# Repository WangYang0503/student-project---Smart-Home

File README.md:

# student-project---Smart-Home
Studienprojekt 16/17: Smart Things

Studienprojekt vom Sommersemester 2016 bis zum Wintersemester 2016/2017 an der Abteilung für Software Engineering des Instituts für Softwaretechnologie an der Universität Stuttgart.

Einführung

Dieses Studienprojekt beschäftigt sich mit der Erstellung eines sogenannten Smart Homes, in dem verschiedene "smarte" Alltagsgegenstände miteinander vernetzt sind und über eine gemeinsame Middleware miteinander kommunizieren. Der Fokus des Projekts liegt dabei auf der Anbindung bestehender Geräte an ein Netzwerk, der Entwicklung weiterer solcher Komponenten und der Implementierung diverser "Wenn-Dann"-Regeln, die das Smart Homes auf seine Umgebung reagieren lassen und es damit überhaupt erst lebendig werden lassen. Viele Bestandteile eines "echten" intelligenten Hauses überschreiten jedoch den Umfang eines Studienprojekts in erheblichem Maße, weshalb an dieser Stelle beispielsweise weder eine Lichtsteuerung am 230V-Stromnetz, noch eine realitätsnahe Tür- oder Garagensteuerung realisiert werden kann. Auch die Aufrüstung eines echten Autos zu einem sogenannten "Smart Car", das den Ausgangspunkt vieler Ideen für ein intelligentes Gerätenetzwerk darstellt, sprengt selbstverständlich den Rahmen. Aus diesem Grund beschränkt sich dieses Studienprojekt bei der Entwicklung der verschiedenen Komponente im Allgemeinen auf Miniatur-Modelle und zweckmäßige Nachbauten. Diese genügen trotzdem, um die notwendigen Schnittstellen für die Geräte zu schaffen, eine grundlegende Implementierung zur Umsetzung der "Wenn-Dann"-Regeln vorzunehmen und dem äußeren Betrachter einen Eindruck über die bestehenden Möglichkeiten in dem Smart Home zu verschaffen.

Das Studienprojekt umfasst die folgenden "Smart Things":

Eine Kaffeemaschine
Ein Smart Car
Eine Haus- und eine Garagentür
Die Innen- und Außenbeleuchtung eines Hauses
Einen Rauchmelder

All diese Gegenstände lassen sich zusätzlich über eine Android-App steuern und kontrollieren. Um diese Geräte in Form von "Wenn-Dann"-Regeln auch tatsächlich auch verknüpfen zu können, kommt ein dafür entwickeltes Backend mit Datenbank und leicht zu bedienender Weboberfläche zum Einsatz.

Bei der Kaffeemaschine handelt es sich im Gegensatz zu den anderen Smart Things nicht um ein Modell, sondern um eine richtige Kaffeemaschine in Lebensgröße, die über eine WLAN-Schnittstelle verfügt und somit auch in das Netzwerk eingebunden werden kann. Um die Interaktion der beiden elektronischen Komponenten im Smart Home besser demonstrieren zu können, wurden die Steuerung der Innen- und Außenbeleuchtung und der Haus- und Garagentür  in ein kleines Holzmodell eines Wohnhauses integriert. Bei dem Smart Car handelt es sich um einen Lego Mindstorms-Roboter, der - als Modell eines autonomen, oder zumindest intelligenten Autos - selbstständig fahren und mit anderen Komponenten des Smart Homes kommunizieren kann. Aufgrund der nur aufwändig herzustellenden realen Testbedingungen zur Auslösung des Rauchmelders wird dieser vollständig über eine Android-App auf einem Smartphone simuliert.

Ein weiterer Schwerpunkt dieses Studienprojekts liegt auf der Durchführung von  Aktivitäten des Safety Engineerings, um sicherzustellen, dass bei einer realen Umsetzung des Modells in Lebensgröße so wenig Gefährdungen wie möglich für die Umwelt auftreten. So wurden in den Entwicklungsprozess des Entwickler-Teams verschiedene safety-spezifische Aktivitäten integriert, die die fortwährende Analyse des Gesamtsystems hinsichtlich Safety-Risiken und deren Beseitigung sicherstellen.

Im Folgenden wird ein Überblick über das Projekt gegeben und auf die Hauptverzeichnisse der einzelnen Smart Things verwiesen, in denen sich dann nähere Informationen zum Aufbau, der Installation, zum Betrieb und den implementierten Schnittstellen und Features befinden.

Übersicht der Komponenten

In dem folgenden Schaubild ist der grundlegende Aufbau des durch das Studienprojekt realisierten Smart-Home-Netzwerks dargestellt:

Middleware

Im Zentrum des Netzwerks steht die Middleware. Sie ist grundlegend für das Verwalten der einzelnen Endgeräte, den Smart Things, zuständig. Sie besteht aus einem Server, auf dem die Kaa IoT Development Platform installiert ist und ausgeführt wird. Sie ist in der Lage Software Development Kits (SDKs) in verschiedenen Programmiersprachen zu generieren, darunter auch SDKs für Java, nachdem die entsprechenden Smart-Things auf der dazugehörigen Weboberfläche des Kaa-Servers spezifiziert worden sind. Diese SDKs enthalten die notwendigen Schnitstellen in der jeweiligen Sprache, um dann in der Software der Endgeräte mit der Kaa-Middleware kommunizieren zu können. Die Endgeräte verbinden sich nach dem Start ihrer Software unter Verwendung der zuvor generierten SKDs automatisch mit der Middleware und können bei Bedarf Nachrichten in Form von Events an diese übermitteln. Der Kaa-Server nimmt Nachrichten von den Endgeräten entgegen und verteilt sie an die momentan verfügbaren Endgeräte, die auf Events dieser Art warten (Listener-Prinzip). Diese Art der Kommunikation greift das Backend auf, um an dieser Stelle die Umsetzung der zuvor durch den Anwender festgelegten "Wenn-Dann-Regeln" sicherzustellen.

--> Verzeichnis im Repository

Backend

Um das Smart-Home nun tatsächlich auch “smart” machen zu können, sodass es in bestimmten Situationen von alleine vordefinierte Aktionen auslöst, genügt die direkte Kommunikation der Smart-Things über die Middleware nicht. In diesem Fall müssten Verknüpfungen zur Kommunikation der Smart-Things untereinander umständlich direkt in dem Quellcode der einzelnen Komponenten implementiert werden und wären folglich ohne Neukompilierung des jeweiligen Projekts nicht durch den Endanwender anpassbar. Da dies natürlich eine sehr unkomfortable Art der Konfiguration des Smart Homes darstellt, übernimmt das Backend diese Aufgabe, in welchem der Benutzer über eine Weboberfläche die Regeln, die für sein Smart Home greifen sollen, einstellen und verwalten kann. Bei diesen Regeln handelt es sich dabei um die bereits angesprochenen “Wenn-Dann-Regeln”: Eine Aktion wird vom Smart-Home dann ausgelöst oder ausgeführt, wenn zuvor ein bestimmtes Ereignis oder eine bestimmte Situation aufgetreten ist.

Das Grundgerüst des Backends besteht aus einem Java-Programm, welches selbst auch ein KAA-SDK besitzt und darüber Zugriff auf die Schnittstellen aller Smart-Things erhält. Es ist somit über entsprechende Listener in der Lage, auf die ausgesendeten Events aller Smart-Things zu reagieren und selbst Events an diese Smart-Things auszusenden, die dann dementsprechend Aktionen auslösen können. Ausgehend von dieser Basis besitzt das Backend eine SQLite-Datenbank, in der die Regeln gespeichert werden können. Eine sogenannte “RuleWorker”-Klasse übernimmt auf dem Server die Aufgabe, auf Eingabe eines Eventnamens aus dieser Datenbank alle passenden Regeln herauszusuchen, die diesen Eventnamen als Trigger-Event gespeichert haben, die dazugehörige Aktionsmethode abzufragen auszulösen.

Das Backend besteht weiter aus einer Webserver-Komponente, die sowohl statische Webseiten ausgeben, als auch Ajax-Requests entgegennehmen, verarbeiten und beantworten kann. Für diese Webserver-Komponente gibt es eine Weboberfläche, die die Möglichkeit bietet, über ein Formular neue Regeln anzulegen, diese in einer Tabelle anzuzeigen, zu editieren, zu löschen, zu aktivieren, zu deaktivieren und sie auch direkt über die Weboberfläche auszuführen, ohne dass das zugehörige Triggerevent dafür ausgelöst werden muss. Ferner steht neben einem persistenten Log, das alle Aktionen des Smart-Homes, sowie alle eingehenden und ausgehenden Events und die jeweils ausgelösten Regeln aufzeichnet, auch ein sogenanntes “Live Log” zu Verfügung, das dem Benutzer in Echtzeit auf der Weboberfläche Informationen über die ausgeführten Regeln bietet.

Kurzum bietet das Backend dem Benutzer des Smart Homes über eine Weboberfläche eine sehr komfortable Möglichkeit, “Wenn-Dann-Regeln” für das Smart-Home nach eigenen Wünschen individuell zu verwalten, die die Art und Weise festlegen, auf der die einzelnen innerhalb dieses Projekts entwickelten Smart-Things miteinander interagieren können.

--> Verzeichnis im Repository

Kaffeemaschine

Die Kaffeemaschine, die in diesem Projekt zum Einsatz kommt, ist bereits werksseitig mit einem WLAN-Modul ausgestattet. Damit dieses genutzt werden kann, ist zunächst die Konfiguration der Verbindung mit dem lokalen WiFi-Netzwerk notwendig, welche über die bereits existierende Android-App des Kaffeemaschinenherstellers erfolgen muss. Im Rahmen dieses Projekts wurde die Kommunikation dieser bereits vorhandenen App mit der Kaffeemaschine über das Netzwerk beobachtet und analysiert, sodass es gelungen ist, die Kommunikation zu großen Teilen zu entschlüsseln und die Hersteller-App damit durch eine eigens entwickelte Software zu ersetzen. Da die Kaffeemaschine aufgrund fehlender Möglichkeiten, diese zu programmieren oder weiter zu konfigureren nicht in der Lage ist, selbstständig mit der Middleware zu kommunizieren, wurde als Teil des Studienprojekts ein Java-Programm, der sogenannte "CoffeeServer", entwickelt, das zum einen die Kommunikation mit der Middleware übernimmt und zum anderen Befehle an die Kaffeemaschine schickt und Statusmeldungen von ihr empfängt, um sie mit dem Smart Home verknüpfen zu können. Dabei wurden sämtliche zuvor entschlüsselte Kommunikationsvorschriften für die Kaffeemaschine in eine Java-Bibliothek ausgelagert ("SmartCoffeeAPI"), die vom CoffeeServer verwendet wird und es erlaubt, über WiFi die Verbindung mit dem WLAN-Modul der Kaffeemaschine aufzubauen, die Maschine anzusteuern und Statusmeldungen von ihr zu empfangen.

Die Kaffeemaschine ist so in der Lage, Statusmeldungen über den aktuellen Zustand (beispielsweise Bereit, Kochend, Mahlend) an die Middleware und damit an andere Smart Things zu senden und gleichtig von diesen Befehle zu empfangen, beispielsweise Kaffee kochen, Brühstärke ändern und Tassenzahl ändern.

--> Verzeichnis im Repository

Smart Car

Das sogenannte "Smart Car" wird in diesem Studienprojekt modellhaft über einen Lego-Mindstorm (EV3) realisiert, der ganz grob die ungefähre Bauform eines Fahrzeugs aufweist. Auf dem "programmieren intelligenten Stein" (Mindstorm-Brick) des Mindstorms, der das logische Herz des Lego-Roboters darstellt, ist das javafähige Betriebssystem Lejos installiert. Damit ist es möglich, Java-Programme auf dem Mindstorm auszuführen. Die EV3-Serie erlaubt zudem den Anschluss eines wifi-fähigen USB-Sticks, über den zusammen mit der entsprechenden Implementierung dann die Kommunikation mit dem Kaa-Server erfolgen kann. Wie bei den meisten anderen der zu dem Studienprojekt gehörenden Smart-Things kann somit das vom Kaa-Server für den Mindstorm generierte SDK in ein Java-Programm eingebettet werden und über das Netzwerk mit der Middleware kommunizieren.

Das Smart Car ist beispielsweise in der Lage selbstständig über Lichtsensorik einer farbigen Linie zu folgen, wenn dies beispielsweise von der App veranlasst wird, auf Befehl anzuhalten, anhand der Linienfarbe zu erkennen, wo sich das Auto gerade aufhält (zum Beispiel, dass es sich in der Nähe der Garage befindet), unter Verwendung  eines drehbaren Ultraschallsensors Hindernissen auszuweichen, aktuelle Statussignale an die Middleware zurückzumelden und unter Verwendung von Bodenmarkierungen in die Garage einzuparken.

--> Verzeichnis im Repository

Haus- und Garagentüren

Die hier zum Einsatz kommenden Türen - jeweils eine Haustüre und eine Garagentüre - sind Teil des Holzmodells eines Hauses, das zur Veranschaulichung dieser Komponente und der Lichtsteuerung angefertigt wurde. Ähnlich wie bei dem Smart Car wird auch hier die Steuerung der beiden Türen über einen Lego-Roboter (EV3) realisiert, dessen Mindstorm-Brick mit einem WiFi-USB-Stick ausgestattet ist und das javafähige Betriebssystem Lejos installiert hat. Die Türen werden über Lego-Motren, die zu diesem Roboter gehören, angesteuert: Eine Konstruktion aus einem Getriebe mit mehreren Zahnrädern erlaubt es dem Motor, die Haustür vorsichtig zu öffnen und wieder zu schließen. Eine Art Flaschenzug mit einer Seilwinde, die an einem Motor auf dem Dach der Garage befestigt ist, erlaubt es einem anderen Motor, der mit demselben Mindstorm verknüpft ist, das Garagentor zu öffnen und zu schließen. Zusätzlich wird der Status des Garagentors (Offen oder Geschlossen) durch einen Ultraschallsensor erfasst.

Die Haus- und Türsteuerung kann so den aktuellen Status der Türen an die Middleware melden und gleichzeitig von anderen Smart Things Befehle empfangen und ausführen, wie das Öffnen und Schließen der Türen.

--> Verzeichnis im Repository

Innen- und Außenbeleuchtung

Neben der Türsteuerung wird das Hausmodell auch mit verschiedenen Lichtern versorgt, die sowohl außen vom Haus, als auch innen in Form von RGB-LEDs angebracht sind. Diese werden über eine Verstärkerplatine, auf der Transistorschaltungen realisiert sind, um die LEDs mit ausreichend Strom zu versorgen, geschaltet. Diese Platine ist wiederum mit einem Raspberry Pi 3 verknüpft, das Raspbian als Betriebssystem verwendet und somit in der Lage ist, über ein darauf ausgeführtes Java-Programm die LEDs über die Verstärkerplatine durch das Ansteuerun der GPIO-Ports an- und auszuschalten. Das Raspberry Pi besitzt bereits werkseitig ein integriertes WLAN-Modul und kann somit direkt mit dem Smart-Home-Netzwerk verknüpft werden und ebenso ein Kaa-SDK verwenden. Die im Rahmen des Studienprojekts erstellte Software auf dem Raspberry Pi unterstützt die Zuordnung der LEDs zu Räumen, sodass verschiedene LED-Gruppen in einem Raum zusammengefasst und dann von anderen Smart Things gemeinsam als Gruppe angesteuert werden können. Die Konfiguration und Aufteilung der LEDs an den verschiedenen Pins in Räume erfolgt dabei über eine XML-Datei, die von der Software auf dem Raspberry zu Beginn eingelesen wird. Da es sich bei den LEDs um RGB-Leds handelt, kann auch die Farbe der Beleuchtung durch die softwareseitige Ansteuerung verändert werden.

Die Lichtsteuerung auf dem Raspberry kann so den aktuellen Status der Beleuchtung (zum Beispiel An, Aus, Farbe, Helligkeit) an die Middleware senden und im Gegenzug Befehle anderer Smart Things entgegennehmen, wie das Dimmen der LED-Helligkeit, das Verändern der Farben und das Ein- und Ausschalten einzelner LEDs oder ganzer zu Räumen zusammengefasster LED-Gruppen.

--> Verzeichnis im Repository

Rauchmelder

Auch ein Rauchmelder soll als Smart Thing in das Smart-Home-Netzwerk integriert werden. Allerdings wurde aus Gründen des Aufwands und der nur schwer herzustellenden notwendigen Testbedingungen darauf verzichtet, einen echten Rauchmelder, wie man ihn aus den Baumärkten kennt, umzurüsten. Stattdessen wird der Rauchmelder über eine Android-App simuliert, die auf einem Smartphone oder Tablet ausgeführt wird. Innerhalb dieser App kann so mit einem Knopfdruck ein Feueralarm ausgelöst werden, dere von einem schrillen Ton begeleitet wird. Der Alarm hält so lange an, bis er durch einen erneuten Knopfdruck in der App deaktiviert wird. Diese App integriert ebenfalls ein Kaa-SDK, das jedoch im Gegensatz zu den bisher verwendeten Java-SDKs speziell auf Android-Geräte ausgerichtet ist. Damit ist auch hier eine direkte Kommunikation über die Middleware zu anderen Smart Things möglich.

Wird bei der Rauchmeldersimulation der Feueralarm ausgelöst, sendet die App ein entsprechendes Event an die Middleware, welches diese wiederum an andere Geräte verteilt, die dann entsprechend auf den Alarm reagieren können, beispielsweise durch Aktivierung einer Notbeleuchtung. Endet der Alarm, wird erneut die Middleware verständigt, um etwaige ergriffene Maßnahmen anderer Smart Things wieder abzubrechen, sofern nötig.

--> Verzeichnis im Repository

Android-App

Als zentrale Benutzerschnittstelle des Smart-Home-Netzwerks wird im Rahmen des Studienprojekts eine Android-App entwickelt, über die alle Smart-Things eingesehen, abgefragt und kontrolliert werden können sollen. Ähnlich wie der Rauchmelder implementiert auch die App ein speziell auf Android ausgelegtes Kaa-SDK, dass es dem Nutzer ermöglicht, über das Netzwerk mit der Middleware zu kommunizieren.

Die App empfängt nahezu alle Kaa-Events der mit dem Netzwerk verknüpften Smart-Things und kann so zu jeder Komponente Statusmeldungen einsehen und Benachrichtigungen dieser reagieren, beispielsweise wenn das Kochen des Kaffees abgeschlossen ist. Darüberhinaus kann über die App auch manuell auf die Smart Things Einfuss genommen werden, um beispielsweise des Starten oder Stoppen des Smart Cars zu veranlassen, Kaffeeeinstellungen zu konfigurieren, Lichter ein-, aus- und umzuschalten oder die Türen zu öffnen oder zu schließen. Darüberhinaus erlaubt es die App, auch Timer für das Kaffeekochen festzulegen, sodass der Benutzer bereits im Voraus konfigurieren kann, zu welcher Uhr- oder Tageszeit automatisch Kaffee gekocht werden soll, sofern natürlich ausreichend Ressourcen wie Kaffee und Wasser vorhanden sind.

--> Verzeichnis im Repository

Integrierte Regeln

Neben der Steuerung der Smart Things über die Android-App ist es eines der Hauptziele dieses Studienprojekts, die Interaktion der intelligenten Geräte untereinander über die Middleware zu realisieren. So sollen nach dem Prinzip der "Wenn-Dann-Regeln" zuvor definierte Aktionen ausgelöst werden, wenn das Smart Home eine bestimmte Situation registriert. Diese Art der Regeldefinition erfolgt von Seiten des Benutzers auf der Weboberfläche des Backends, welches im Anschluss dann in der Lage ist, auch diese Regeln anzuwenden. "Wenn das Smart Car am Smart Home ankommt, soll die Kaffeemaschine Kaffee kochen, damit der Besitzer diesen trinken kann, wenn er das Haus betritt." ist ein typisches Beispiel für eine solche Regel.

Unabhängig von der Android-App wurden die folgenden Interaktionen ihm Rahmen dieses Projekts implementiert:

Wenn-Dann-Regel
Auslösende Komponente
Reagierende Komponente
Anmerkungen

Wenn das Auto am Smart Home ankommt, soll Kaffee gekocht werden.
Smart Car
Kaffeemaschine
Der Grundgedanke bei dieser Regel ist, dass sich der Besitzer des Smart Homes nach einem anstrengenden Arbeitstag bei einer Tasse frischem Kaffee entspannen möchte, sobald er zu Hause angekommen ist.

Wenn das Auto an der Garage ankommt, soll sich das Garagentor öffnen.
Smart Car
Türsteuerung
Wenn das Auto die Garage erreicht, ist davon auszugehen, dass es auch in die Garage eingeparkt werden soll. Deshalb öffnet sich das Tor automatisch, um dem Besitzer lästiges manuelles Öffnen zu ersparen.

Wenn ein Feueralarm ausgelöst wird, soll die Hausbeleuchtung eingeschaltet werden und rot leuchten.
Rauchmelder
Lichtsteuerung
Durch das Einschalten der Beleuchtung soll dem Besitzer des Smart Homes zum einen das Haus ausgeleuchtet werden, damit er sich auch nachts sofort in der Notsituation zurecht finden kann und nicht erst den Lichtschalter suchen muss; zum anderen soll ihm mit dem roten Leuchten, wie man es auch aus Science-Fiction-Filmen kennt, zusätzlich der Ernst der Lage deutlichgemacht werden.

Wenn ein Feueralarm ausgelöst wird, sollen die Haus- und Garagentüre geöffnet werden.
Rauchmelder
Türsteuerung
Um dem Besitzer des Smart Homes im Falle eines Feueralarms frühzeitig mögliche Fluchthindernisse aus dem Weg zu räumen, sollen die Haus- und die Garagentüre automatisch geöffnet werden.

Die "Auslösende Komponente" bezeichnet das Smart Thing, das die "Wenn"-Aufgabe der Regel übernimmt und die Situation erkennt, auf die reagiert werden soll. Die "Reagierende Komponente" bezeichnet dagegen das Smart Thing, das den "Dann"-Teil der Regel übernimmt und auf die eingetretene Situation mit einer zuvor definierten Aktion reagiert.

Technische Übersicht

In Laufe des Projekts wurden einige verschiedene Techniken und Entwicklungswerkzeuge eingesetzt. An dieser Stelle soll darüber eine Übersicht gewährt werden.

Java

Der allergrößte Teil der Software dieses Projekts ist in Java 8 geschrieben. Dies betrifft vor allem die Software der Kaffeemaschine, bestehend aus dem CoffeeServer und der SmartCoffeeAPI, und die Lichtsteuerung, welche in "reinem" Java, also ohne weitere plattformabhängige Bibliotheken und Erweiterungen, verfasst sind. Die Software der Kaffeemaschine kann damit als ausführbare JAR-Datei auf einem nahezu beliebigen Rechner ausgeführt werden. Im Rahmen des Studienprojekts wurde speziell ein Raspberry PI 3 (Model B) mit installierter JRE als Zielplattform für den CoffeeServer vorgesehen, auf dem dann auch die Lichtsteuerung ausgeführt werden soll, die die GPIO-Pins des Raspberrys verwendet, um die LEDs, die die Beleuchtung des Smart Homes repräsentieren, über eine Verstärkerplatine anzusteuern. Als Entwicklungsumgebungen wurden hierfür IntelliJ IDEA von JetBrains und Eclipse eingesetzt.

Android

Die App zur Gesamtsteuerung und der Rauchmelder-Simulator sind Android-Apps, die in Java 8 geschrieben worden sind. Zur Ausführung auf Android-Geräten setzen diese ein Minimum-Android-SDK-Level von 16 ("Jelly Bean") voraus, Ziel-SDK-Level ist 24 ("Nougat"). Zur Entwicklung wurde ausschließlich Android Studio von JetBrains eingesetzt, die Apps werden in diesem mit Gradle gebuildet.

LeJOS

Das Smart Car und die Türsteuerung für die Haus- und Garagentüre sind jeweils über einen Lego-Mindstorm EV3 realisiert, über deren "intelligenten Stein" die Kommunikation mit der Middleware umgesetzt wird und die die dazugehörenden Lego-Sensoren und Lego-Motoren einsetzen, um die Umgebung zu erfassen und zu beeinflussen. Da der Kaa-Server auf der Middleware nur für bestimmte Programmiersprachen SDKs generieren kann, die für die Software der Smart Things zwingend notwendig sind, um mit der Middleware interagieren zu können, war es erforderlich, das Standardbetriebssystem der Mindstorms, das nur C-ähnliche Programme ausführen kann, zu entfernen und stattdessen das Betriebssystem LeJOS (LeJOS EV3 0.9.1-beta) über eine SD-Karte aufzuspielen, das die Ausführung von Java-Programmen als ausführbare JAR-Dateien ermöglicht, die mit einer entsprechenden API für EV3-Mindstorms ausgestattet worden sind. Als Entwicklungsumgebungen wurden hierfür IntelliJ IDEA von JetBrains und Eclipse eingesetzt.

Maven

Als Build-Management-Tool wird in diesem Studienprojekt Apache Maven eingesetzt, das zahlreiche zentrale Aufgaben übernimmt und dessen Zyklus jeweils für jedes Smart Thing in ein eigenes Submodul aufgeteilt ist. Sämtliche Kaa-SDKs werden bei einem Aufruf von Mavens Goal "clean install" zunächst aus dem Sammelordner für die SKDs in das lokale Maven-Repository installiert und stehen dann den anderen Komponenten, die die entsprechenden SDKs als Abhängigkeit eingetragen haben, zum Kompilieren zur Verfügung. Nach der Installation dieser SDKs buildet der Maven-Prozess die Software und erstellt aus dem CoffeeServer, welcher abhängig von der SmartCoffeeAPI ist, der Lichtsteuerung, der Software für das SmartCar und der Software für die Türsteuerung jeweils ausführbare JAR-Dateien, welche in einen build-Ordner im Hauptverzeichnis kopiert werden. Dabei werden bestehende softwaretechnische Abhängigkeiten und zusätzlich benötigte APIs, wie beispielsweise LeJOS "ev3classes" für die Programmierung der EV3-Mindstorms in Java und die zahlreichen Kaa-SDKs, berücksichtigt und mit in die JAR-Dateien gepackt ("jar with dependencies"). Auch die beiden Android-Apps (App zur Hauptsteuerung und Rauchmelder) werden zu APK-Dateien gebuildet; das geschieht allerdings über das in Android-Studio eingebettete Gradle, dessen Build-Prozess jeweils von Maven mitgestartet wird. Abhängigkeiten der Android-Apps sind daher nicht in Maven direkt integriert, sondern in den dazugehörigen Gradle-Build-Dateien in Android Studio. Die generierten APK-Dateien werden nach Abschluss der Kompilierung ebenfalls in den zentralen Build-Ordner im Hauptverzeichnis kopiert.

Bevor die einzelnen Software-Komponenten gebuildet werden, führt Maven jeweils etwaige angelegte Unit-Tests und statische Codeanalysen mittels Checkstyle und FindBugs durch und reklamiert etwaige Testfehlverschläge, Verstöße gegen den als Checkstyle-XML-Datei definierten Styleguide oder gefundene Bug-Muster.

Bei den Smart Things, die auf einem Lego Mindstorms ausgeführt werden - also dem Smart Car und der Türsteuerung - ist es notwendig, die generierten ausführbaren JAR-Dateien auf den im selben Netzwerk befindlichen Lego-Mindstorm mittels SCP zu kopieren. Auch dies kann Maven auf Wunsch übernehmen: Durch einen Aufruf des Goals "clean intall antrun:run" im Unterverzeichnis des jeweiligen SmartThings wird die JAR-Datei generiert und automatisch auf den "intelligenten Stein" kopiert, wo sie dann manuell über den LeJOS-Explorer auf dem Mindstorm ausgeführt werden kann.

Weitere Infos zu Maven und dem Build-Management befinden sich im Dokumentationsordner über das Build-Management im Repository in Form einer Präsentation.

Git

Git ist die Software zu Versionsverwaltung, die in dem Studienprojekt zum Einsatz kommt. Als Webanwendung für das zentrale Git-Repository auf dem Uniserver kommt GitLab zum Einsatz, welches mit JIRA von Atlassian, der von den Projektteilnehmern verwendeten Webanwendung zum Bugtracking und Projektmanagement, direkt verschaltet ist. Auf diese Weise kann des Bugtracking und Umsetzen von User Stories und Tasks anhand der Commit-Messages analog zu den Commits im zentralen Git-Repository vorgenommen werden.

Die zentrale ".gitignore"-Datei befindet sich im Hauptverzeichnis des Repositories.

Jenkins

Um das gesamte Projekt fortlaufend nach jedem Commit anhand des Maven-Zyklusses automatisiert bauen und so frühzeitig Inkompatiblitäten und Softwarefehler erkennen zu können, kommt bei diesem Studienprojekt Jenkins als Continuous-Integration-Server zum Einsatz. Dieser Uni-Server hat direkten Zugriff auf das zentrale Git-Repository und kann so den Build-Prozess direkt nach jedem Commit anhand der vom Repository bezogenen Dateien ausführen.

Im Falle eines Build-Fehlschlags aufgrund von im Maven-Zyklus aufgetretenen Fehlern werden die Teilnehmer des Studienprojekts umgehend per E-Mail über die bestehenden Proleme unterrichtet, damit diese möglichst zeitnah behoben werden können.

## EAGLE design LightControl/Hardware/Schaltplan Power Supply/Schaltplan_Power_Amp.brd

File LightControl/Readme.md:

# LightControl
## Beschreibung
Bei diesem Smart Thing handelt es sich um eine von uns in verminderter Größe hergestellten Simulation der Beleuchtung in einem SmartHome. Durch diese Simulation können wir Lichter im Haus ansteuern und leuchten lassen. Die Farbe der LEDs lässt sich über die App einstellen. Auch durch den SmokeDeviceAlarm können die LEDs zum Leuchten gebracht werden. Innerhalb dieses Projekts war es das Ziel, die Beleuchtung zu planen, zu erstellen und dann die Steuerung zu programmieren. Auch war die Kommunikation der Steuerungmit der App und dem Netzwerk wichtig. 

## Funktionen
Die LightControl besitzt folgende Funktionen:
### Befehle an die LightControll
Die LightControl wartet fortlaufend auf Befehle, die über die Middleware bei ihr eintreffen und reagiert anschließend auf diese. Folge Befehle können an die Garage gesendet werden:
- Lights on: Lichter gehen an.
- Lights off: Lichter gehen aus.
- Lights alarm: Lichter gehen an, da der Rauchmelder Alarm geschlagen hat.

### Informationen von der LightControl
Die LightControl besitzt verschiedene Zustände, die abgefragt werden können:
- LEDInfoRequest
- LEDInfObject(*ID,isRGB,red,green,blue,brightness*)
- LEDInfoResponse(*LEDInfoList*)
- RoomInfoRequest
- RoomInfoReponse(*RoomInfoList*)
- addRoom(*roomID*)
- removeRoom(*roomID*)
- addLight(*lightID,roomID,slot*)
- addRGBLight(*lightID,roomID,slotRed,slotGreen,slotBlue*)
- removeLight(*lightID*)
- setBrightness(*lightID,brightness*)
- setcolor(*lightID,red,green,blue*)
- setRoomBrightness(*roomID,brightness*)
- setRoomColor(*roomID,red,green,blue*)

## Installation und Betrieb
Um die Lichtersteuerung zu benutzen, muss sie am Strom angeschlossen sein. Zudem muss der [Raspberry Pi](https://www.raspberrypi.org/) angeschlossen sein. Nun kann man die Lichter über die App steuern. [Anleitung](https://gilbert.informatik.uni-stuttgart.de/StuPro2016/SmartHomeMain/blob/dev/LightControl/readme.txt)

## Aufbau
Die LightControl besteht aus einem Raspberry Pi, LEDs und einer Verstärkerplatine.

### Hardware
Bei der in diesem Projekt verwendeten Raspberry Pi handelt es sich um einen [Raspberry Pi 3](https://www.raspberrypi.org/products/raspberry-pi-3-model-b/ "Website über den Raspberry Pi 3") EV3 des Herstellers [Raspberry](https://www.raspberrypi.org/ "Webseite des Raspberry"). 

### Kaa-Schnittstelle

#### Ausgehend

| Event | Syntax | Parameter | Beschreibung |
|-------|--------|-----------|--------------|
| LEDinfoResponse | InfoResponseEvent(LEDInfoList) | LEDInfoList(smart_things.light.schema.LEDInfoObjekt) |Dieses Event wird gesendet sobald die Middleware Kaa ein InfoRequesrEvent sendet. |
| RoomInfoResponseEvent |  RoomInfoResponseEvent(RoomInfoList) | RoomInfoList(array,items string) |Dieses Event wird gesendet sobald die Middleware Kaa ein RoomInfoRequestEvent sendet. |

#### Eingehend

| Event | Syntax | Parameter | Beschreibung |
|-------|--------|-----------|--------------|
| LEDInfoObjekt | LEDInfoObjekt(ID,isRGB,red,green,blue,brightness) | ID(string),isRGB(boolean),red(int),green(int),Blue(int),brightness(int) |Dieses Event wird empfangen sobald die Middleware Kaa die Lichter ansteuert. |
| RoomInfoRequest | -- | -- |Dieses Event wird empfangen sobald die Middleware Kaa Informationen über die Räume verlangt. |
| addRoom | addRoom(roomID)  | roomID(int)  |Dieses Event wird empfangen sobald über die App ein neuer Raum erstellt wird. |
| removeRoom | removeRoom(roomID)  | roomID(int) |Dieses Event wird empfangen sobald über die App ein Raum gelöscht wird. |
| addLight | addLight(lightID) | lightID(int),roomID(int),slot(int) | Dieses Event wird empfangen sobald über die App ein neues Licht eingerichtet wird. |
| addRGBLight | addRGBLight(lightID,roomID,slotRed,slotGreen,slotBlue) | lightID(int),roomID(int),slotRed(int),slotGreen(int),slotBlue(int) |Dieses Event wird empfangen sobald über die App ein neues farbiges LED eingerichtet wird. |
| removeLight | removeLight(lightID) | lightID(int) | Dieses Event wird empfangen sobald über die App ein bestimmtes Licht entfernt wird. |
| setBrightness | setBrightness(lightID,brightness) | lightID(int),brightness(int) |Dieses Event wird empfangen wenn über die App die Helligkeit der LEDs geändert wird. |
| setColor | setColor(lightID,red,green,blue) | lightID(int),red(int),blue(int) |Dieses Event wird empfangen wenn der Benutzer über die App die Farbe eines bestimmten Lichtes ändert. |
| setRoomBrightness | setRoomBrightness(roomID,brightness) | roomID(int),brightness(int) |Dieses Event wird empfangen wenn der Benutzer über die App die Helligkeit in einem ganzen Raum ändert. |
| setRoomColor | setRoomColor(roomID,red,green,blue) | roomID(int),red(int),green(int),blue(int) |Dieses Event wird empfangen sobald der Benutzer der App die Farbe der LEDs in einem kompletten Raum ändert. |

## Anmerkungen
Netzteil ist intern von einem Teammitglied und sollte durch eines der Universität ersetzt werden.

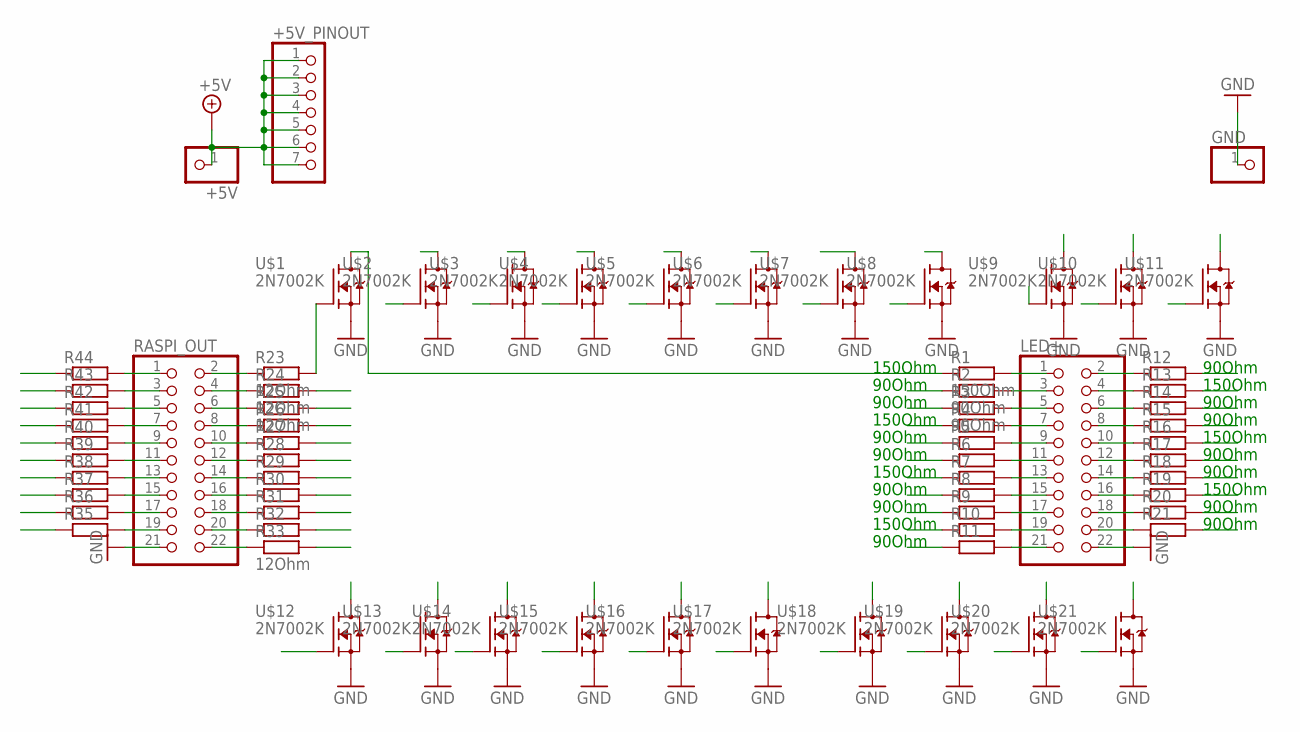
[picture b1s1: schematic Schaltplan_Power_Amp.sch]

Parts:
+5V: PINHD-1X1; 1X01
+5V_PINOUT: PINHD-1X7; 1X07
GND: PINHD-1X1; 1X01
LED+: PINHD-2X11; 2X11
R1: 150Ohm; M1206
R2, R3: 90Ohm; M1206
R4, R5, R6, R7, R8, R9, R10, R11, R12, R13, R14, R15, R16, R17, R18, R19, R20, R21, R26, R27, R28, R29, R30, R31, R32, R35, R36, R37, R38, R39, R40, R41, R42, R43, R44: R-EU_M1206; M1206
R23, R24, R25, R33: 12Ohm; M1206
RASPI_OUT: PINHD-2X11; 2X11
U$1, U$2, U$3, U$4, U$5, U$6, U$7, U$8, U$9, U$10, U$11, U$12, U$13, U$14, U$15, U$16, U$17, U$18, U$19, U$20, U$21: 2N7002K; SOT23

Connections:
+5V: +5V.1, +5V_PINOUT.1, +5V_PINOUT.2, +5V_PINOUT.3, +5V_PINOUT.4, +5V_PINOUT.5, +5V_PINOUT.6, +5V_PINOUT.7
DRAIN2: R2.1, U$2.3 (D)
DRAIN3: R3.1, U$3.3 (D)
DRAIN4: R4.1, U$4.3 (D)
DRAIN5: R5.1, U$5.3 (D)
DRAIN6: R6.1, U$6.3 (D)
DRAIN7: R7.1, U$7.3 (D)
DRAIN8: R8.1, U$8.3 (D)
DRAIN9: R9.1, U$9.3 (D)
DRAIN10: R10.1, U$10.3 (D)
DRAIN11: R11.1, U$11.3 (D)
DRAIN12: R12.2, U$12.3 (D)
DRAIN13: R13.2, U$13.3 (D)
DRAIN14: R14.2, U$14.3 (D)
DRAIN15: R15.2, U$15.3 (D)
DRAIN16: R16.2, U$16.3 (D)
DRAIN17: R17.2, U$17.3 (D)
DRAIN18: R18.2, U$18.3 (D)
DRAIN19: R19.2, U$19.3 (D)
DRAIN20: R20.2, U$20.3 (D)
DRAIN21: R21.2, U$21.3 (D)
GATE2: R24.2, U$2.1 (G)
GATE3: R25.2, U$3.1 (G)
GATE4: R26.2, U$4.1 (G)
GATE5: R27.2, U$5.1 (G)
GATE6: R28.2, U$6.1 (G)
GATE7: R29.2, U$7.1 (G)
GATE8: R30.2, U$8.1 (G)
GATE9: R31.2, U$9.1 (G)
GATE10: R32.2, U$10.1 (G)
GATE11: R33.2, U$11.1 (G)
GATE12: R44.1, U$12.1 (G)
GATE13: R43.1, U$13.1 (G)
GATE14: R42.1, U$14.1 (G)
GATE15: R41.1, U$15.1 (G)
GATE16: R40.1, U$16.1 (G)
GATE17: R39.1, U$17.1 (G)
GATE18: R38.1, U$18.1 (G)
GATE19: R37.1, U$19.1 (G)
GATE20: R36.1, U$20.1 (G)
GATE21: R35.1, U$21.1 (G)
GND: GND.1, LED+.22, RASPI_OUT.21, U$1.2 (S), U$2.2 (S), U$3.2 (S), U$4.2 (S), U$5.2 (S), U$6.2 (S), U$7.2 (S), U$8.2 (S), U$9.2 (S), U$10.2 (S), U$11.2 (S), U$12.2 (S), U$13.2 (S), U$14.2 (S), U$15.2 (S), U$16.2 (S), U$17.2 (S), U$18.2 (S), U$19.2 (S), U$20.2 (S), U$21.2 (S)
unnamed: R44.2, RASPI_OUT.1
unnamed: R43.2, RASPI_OUT.3
unnamed: R42.2, RASPI_OUT.5
unnamed: R41.2, RASPI_OUT.7
unnamed: R40.2, RASPI_OUT.9
unnamed: R39.2, RASPI_OUT.11
unnamed: R38.2, RASPI_OUT.13
unnamed: R37.2, RASPI_OUT.15
unnamed: R36.2, RASPI_OUT.17
unnamed: R35.2, RASPI_OUT.19
unnamed: R23.1, RASPI_OUT.2
unnamed: R24.1, RASPI_OUT.4
unnamed: R25.1, RASPI_OUT.6
unnamed: R26.1, RASPI_OUT.8
unnamed: R27.1, RASPI_OUT.10
unnamed: R28.1, RASPI_OUT.12
unnamed: R29.1, RASPI_OUT.14
unnamed: R30.1, RASPI_OUT.16
unnamed: R31.1, RASPI_OUT.18
unnamed: R32.1, RASPI_OUT.20
unnamed: R33.1, RASPI_OUT.22
unnamed: LED+.1, R1.2
unnamed: LED+.3, R2.2
unnamed: LED+.5, R3.2
unnamed: LED+.7, R4.2
unnamed: LED+.9, R5.2
unnamed: LED+.11, R6.2
unnamed: LED+.13, R7.2
unnamed: LED+.15, R8.2
unnamed: LED+.17, R9.2
unnamed: LED+.19, R10.2
unnamed: LED+.21, R11.2
unnamed: LED+.2, R12.1
unnamed: LED+.4, R13.1
unnamed: LED+.6, R14.1
unnamed: LED+.8, R15.1
unnamed: LED+.10, R16.1
unnamed: LED+.12, R17.1
unnamed: LED+.14, R18.1
unnamed: LED+.16, R19.1
unnamed: LED+.18, R20.1
unnamed: LED+.20, R21.1
unnamed: R23.2, U$1.1 (G)
unnamed: R1.1, U$1.3 (D)

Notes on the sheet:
150Ohm
90Ohm

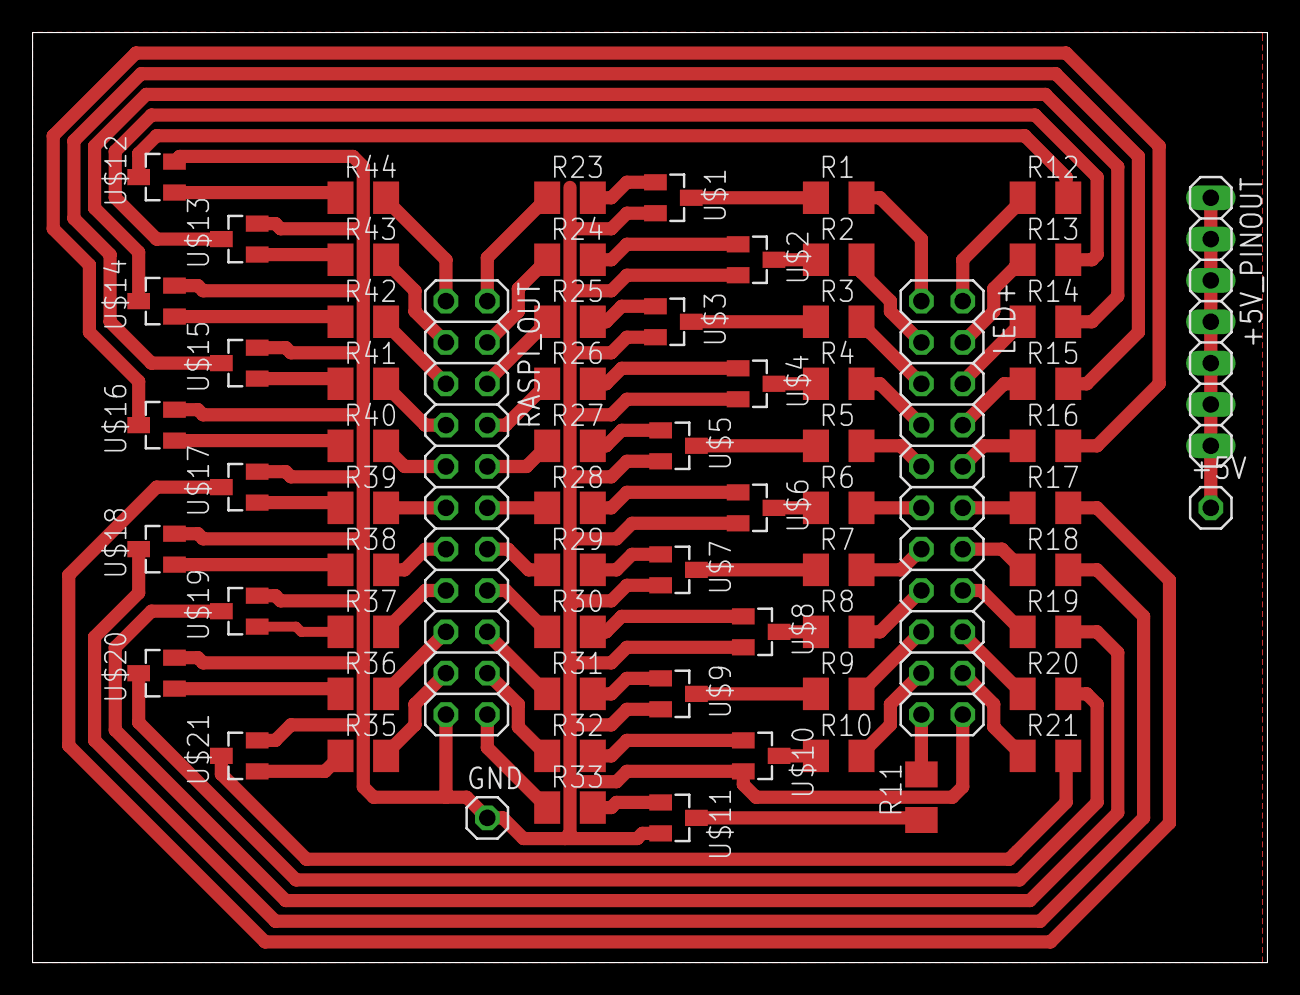
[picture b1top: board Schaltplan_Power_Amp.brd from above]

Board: 2 copper layers, 75.9 x 57.1 mm, 68 parts (0 on the bottom side), 86 nets.
